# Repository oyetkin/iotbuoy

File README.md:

# IoT Buoy

Lake Erie Algae Bloom 2019, (Image credit NOAA)

An open source, low-cost envirnmental buoy designed to monitor the health of lakes, rivers, estuaries and tidal regions with particular emphasis on algae blooms.
Designed by [Analytical Mechanics Associates](https://www.ama-inc.com/) and the [Virginia Modeling, Analysis & Simulation Center (VMASC)](https://www.odu.edu/vmasc). This project is compatible with the [Open Data Cube](https://www.opendatacube.org/), which is an open-source platform that can ingest data from a variety of sensors and has the goal of making environmental monitoring simple and highly accessible. An overview of the current progress is posted [here](https://github.com/oyetkin/iotbuoy/blob/main/BuoyPresentation1.pdf)

# Building your Buoy - Buoy Specific Hardware Required

### 1. [Arduino MEGA or ELEGOO MEGA](https://www.amazon.com/ELEGOO-ATmega2560-ATMEGA16U2-Arduino-Compliant/dp/B01H4ZDYCE/ref=asc_df_B01H4ZDYCE/?tag=hyprod-20&linkCode=df0&hvadid=309751315916&hvpos=&hvnetw=g&hvrand=11900577637582741809&hvpone=&hvptwo=&hvqmt=&hvdev=c&hvdvcmdl=&hvlocint=&hvlocphy=9008124&hvtargid=pla-493625544636&psc=1&tag=&ref=&adgrpid=67183599252&hvpone=&hvptwo=&hvadid=309751315916&hvpos=&hvnetw=g&hvrand=11900577637582741809&hvqmt=&hvdev=c&hvdvcmdl=&hvlocint=&hvlocphy=9008124&hvtargid=pla-493625544636)

- [Arduino MEGA R3](https://store.arduino.cc/usa/mega-2560-r3)

- [ELEGOO MEGA R3 (cheaper)](https://www.amazon.com/ELEGOO-ATmega2560-ATMEGA16U2-Arduino-Compliant/dp/B01H4ZDYCE/ref=asc_df_B01H4ZDYCE/?tag=hyprod-20&linkCode=df0&hvadid=309751315916&hvpos=&hvnetw=g&hvrand=11900577637582741809&hvpone=&hvptwo=&hvqmt=&hvdev=c&hvdvcmdl=&hvlocint=&hvlocphy=9008124&hvtargid=pla-493625544636&psc=1&tag=&ref=&adgrpid=67183599252&hvpone=&hvptwo=&hvadid=309751315916&hvpos=&hvnetw=g&hvrand=11900577637582741809&hvqmt=&hvdev=c&hvdvcmdl=&hvlocint=&hvlocphy=9008124&hvtargid=pla-493625544636)

### 2. [Adafruit Boost Converter](https://www.amazon.com/Module-Output-Voltage-Converter-Regulator/dp/B08NCM9ZPQ/ref=pd_lpo_2?pd_rd_i=B08NCM9ZPQ&th=1)

### 3. [SIM 808 GPRS/GSM Shield](https://www.robotshop.com/en/sim808-gps-gprsgsm-arduino-shield-mkf.html)

### 4. [Adafruit Solar Charger](https://www.adafruit.com/product/390?gclid=Cj0KCQiAkZKNBhDiARIsAPsk0Wjwwub03ZPgBxlKg1lHWn5nn0opyzVy_Q3VPSugYz3q11KsZ251EOcaAhBzEALw_wcB)

### 5. [Adafruit Data Logging Shield](https://www.adafruit.com/product/1141?gclid=EAIaIQobChMI9OqQ1tr58QIVzXxvBB3GTgbGEAQYASABEgITQvD_BwE)

- Requires [CR1220 Coin Cell Battery](https://www.grainger.com/product/54ZU79?ef_id=CjwKCAjwmeiIBhA6EiwA-uaeFeCfQyJyafe8bUuabPpTv9V-Dkiohqq99VO3asoSj661ExP630XgBhoCccUQAvD_BwE:G:s&s_kwcid=AL!2966!3!496359975085!!!g!484329633033!&gucid=N:N:PS:Paid:GGL:CSM-2293:99F1R6:20501231&gclid=CjwKCAjwmeiIBhA6EiwA-uaeFeCfQyJyafe8bUuabPpTv9V-Dkiohqq99VO3asoSj661ExP630XgBhoCccUQAvD_BwE&gclsrc=aw.ds)

- [Adafruit Data Logging Shield Board and Schematic](https://github.com/adafruit/Data-Logger-shield)

- [Adafruit Data Logging Shield Fritzing Object](https://github.com/adafruit/Fritzing-Library/blob/master/parts/Adafruit%20Datalogger%20Shield%20v1.fzpz)

### 6. [Adafruit ADS1115 Analog to Digital Converter](https://www.adafruit.com/product/1085?gclid=Cj0KCQjw0emHBhC1ARIsAL1QGNfJ3SJ85uZqejbk4At3gi_rBteSZwTxbq5_mKbJvcHG9wJhS_kqJ54aAu4vEALw_wcB)

- [ADS1115 Hardware Drivers](https://github.com/adafruit/Adafruit_ADS1X15)

- [ADS1115 Board and Schematics](https://github.com/adafruit/ADS1X15-Breakout-Board-PCBs)

- [ADS1115 Fritzing Object](https://github.com/adafruit/Fritzing-Library/blob/master/parts/Adafruit%20ADS1115%2016Bit%20I2C%20ADC.fzpz)

- [ADS1115 Data Sheet](https://cdn-shop.adafruit.com/datasheets/ads1115.pdf)

- [ADS1115 Sample Code](https://learn.adafruit.com/adafruit-4-channel-adc-breakouts/arduino-code)

### 7. [Adafruit 6V 3.5W Solar Panel](https://www.adafruit.com/product/500)

- [Solar Panel Technical Drawing](https://github.com/VoltaicEngineering/Solar-Panel-Drawings/blob/master/Voltaic%20Systems%203.5W%206V%20113x210mm%20DRAWING%20CURRENT%202017%207%2020.pdf)

### 10. [6600 mAh 3.7V Lithium Ion Battery](https://www.adafruit.com/product/353)

### 11. [Adafruit TPL5110 Breakout Board](https://www.adafruit.com/product/3435)

### 12. [Adafruit Power Boost 1000 Breakout Board](https://www.adafruit.com/product/2465?gclid=CjwKCAiA24SPBhB0EiwAjBgkhrGJI_mgLnF6EL7C2EgxJwRfddbmznOh6DxHYULQIVquQbLt4znxhRoCKecQAvD_BwE)

### 12. Housing
- Buoy with CAD files provided [here](https://github.com/oyetkin/iotbuoy/tree/main/CAD_Files)

- Waterproof box

- Your own design

# Fluorometer Design

### 1. [1 x 395 nm LED](https://www.mouser.com/ProductDetail/BIVAR/UV5TZ-390-15?qs=sGAEpiMZZMtaWn5d0uiAD8cVjFdgDZGx%2FUxBqCDWrPM%3D)

### 2. [FDS 100 Photodiode](https://www.thorlabs.us/thorproduct.cfm?partnumber=FDS100)

### 3. [550 nm Cut On Long Pass Filter](https://www.newport.com/p/10CGA-550)

### 4. [Jewler's Resin](https://www.amazon.com/16OZ-Epoxy-Resin-Graduated-Instructions/dp/B0839GN3PF/ref=sr_1_5?keywords=clear%2Bepoxy%2Bresin&qid=1638217693&qsid=146-2373950-0512811&s=arts-crafts&sr=1-5&sres=B08233BV5W%2CB08HN2XCDS%2CB0839GN3PF%2CB098918WFB%2CB084PZG6HK%2CB07S1MLQMJ%2CB084Q87Y8M%2CB07YCVVYFK%2CB099XFL1PK%2CB086L1CDMT%2CB07G5HY79C%2CB07JBKDQZJ%2CB07JB5P76Z%2CB089XZJFG5%2CB097JLGFZF%2CB07QF2XYYX%2CB092HX7SQT%2CB08PF576QC%2CB0823LC5H1%2CB08XQ2S1VQ&th=1)

### 5. [Black ABS Filament (will be useful for turbidity sensor as well)](https://www.amazon.com/HATCHBOX-3D-Filament-Dimensional-Accuracy/dp/B00J0H8EWA/ref=sr_1_3?crid=HBAP4Q1YHOWB&keywords=black%2Babs%2Bfilament%2B1.75%2B1kg&qid=1638217775&qsid=146-2373950-0512811&sprefix=black%2Babs%2Bfila%2Carts-crafts%2C167&sr=8-3&sres=B00J0H8EWA%2CB07XF5KM74%2CB07T2QZSLY%2CB01M6Y2QF1%2CB00MV7T25E%2CB07199449V%2CB00WX4UONO%2CB0919Q91MN%2CB015VGJGPW%2CB00F9MNMAY%2CB018F586ES%2CB08N4MMK6V%2CB089NPTH2W%2CB09H7RKL95%2CB07GFXYVLR%2CB08BR7YCY1&srpt=THERMOPLASTIC_FILAMENT&th=1)

# Turbidity Sensor Design

### 1. [2 x Photoresistors](https://www.amazon.com/gp/product/B01N7V536K/ref=ppx_yo_dt_b_search_asin_image?ie=UTF8&psc=1)

### 2. [1 x RGB LED](https://www.amazon.com/gp/product/B077XGF3YR/ref=ppx_yo_dt_b_search_asin_title?ie=UTF8&th=1)

### 3. [Jewler's Resin](https://www.amazon.com/16OZ-Epoxy-Resin-Graduated-Instructions/dp/B0839GN3PF/ref=sr_1_5?keywords=clear%2Bepoxy%2Bresin&qid=1638217693&qsid=146-2373950-0512811&s=arts-crafts&sr=1-5&sres=B08233BV5W%2CB08HN2XCDS%2CB0839GN3PF%2CB098918WFB%2CB084PZG6HK%2CB07S1MLQMJ%2CB084Q87Y8M%2CB07YCVVYFK%2CB099XFL1PK%2CB086L1CDMT%2CB07G5HY79C%2CB07JBKDQZJ%2CB07JB5P76Z%2CB089XZJFG5%2CB097JLGFZF%2CB07QF2XYYX%2CB092HX7SQT%2CB08PF576QC%2CB0823LC5H1%2CB08XQ2S1VQ&th=1)

### 4. [Black ABS Filament (will be useful for fluorometer as well)](https://www.amazon.com/HATCHBOX-3D-Filament-Dimensional-Accuracy/dp/B00J0H8EWA/ref=sr_1_3?crid=HBAP4Q1YHOWB&keywords=black%2Babs%2Bfilament%2B1.75%2B1kg&qid=1638217775&qsid=146-2373950-0512811&sprefix=black%2Babs%2Bfila%2Carts-crafts%2C167&sr=8-3&sres=B00J0H8EWA%2CB07XF5KM74%2CB07T2QZSLY%2CB01M6Y2QF1%2CB00MV7T25E%2CB07199449V%2CB00WX4UONO%2CB0919Q91MN%2CB015VGJGPW%2CB00F9MNMAY%2CB018F586ES%2CB08N4MMK6V%2CB089NPTH2W%2CB09H7RKL95%2CB07GFXYVLR%2CB08BR7YCY1&srpt=THERMOPLASTIC_FILAMENT&th=1)

# Other Items Required

- SD Card
- Jumper wires
- Header pins
- Solder
- Soldering iron
- Wire strippers
- Heat shrink tubing
- Electrical tape
- DP 100 epoxy
- Rope/anchor OR Rope/mooring OR free-floating

# Other Interesting Sensors

- [BME 680 Temperature, Pressure and Humidity Sensor](https://www.adafruit.com/product/3660)

- [DHT-11 Temperature/Humidity Sensor](https://www.adafruit.com/product/386)

- [DHT-22 Temperature/Humidity Sensor](https://www.adafruit.com/product/385)

- [Waterproof Thermistor](https://www.adafruit.com/product/372)

- [pH Sensor - TEKCOPLUS](https://www.amazon.com/Replacement-Electrode-Connector-Controller-Hydroponics/dp/B09681C36B/ref=sr_1_19?dchild=1&keywords=ph+meter+electrode&qid=1629149917&sr=8-19)
OR
- [pH Sensor - Vernier](https://www.vernier.com/product/ph-sensor/)

- [Turbidity Sensor](https://www.digikey.com/en/products/detail/amphenol-advanced-sensors/TSD-10/4767843?utm_adgroup=Sensors%20%26%20Transducers&utm_source=google&utm_medium=cpc&utm_campaign=Dynamic%20Search_EN_RLSA_Buyers&utm_term=&utm_content=Sensors%20%26%20Transducers&gclid=CjwKCAjwmeiIBhA6EiwA-uaeFRJvJ3rLHPiHJND-PSO5aePXsmi2i962wfCCjfp96LtXLJMJ6MAUsBoClz0QAvD_BwE)

- [MPU 6050 Inertial Measurement Unit (for wave height, direction etc.)](https://www.adafruit.com/product/3886)

# Fabrication

- Read the "Complete Guide to Building Your Very Own Algae Monitoring Buoy"

# Viewing Results

- Download jupyter to your computer and run "Visualization_Notebook.ipynb"

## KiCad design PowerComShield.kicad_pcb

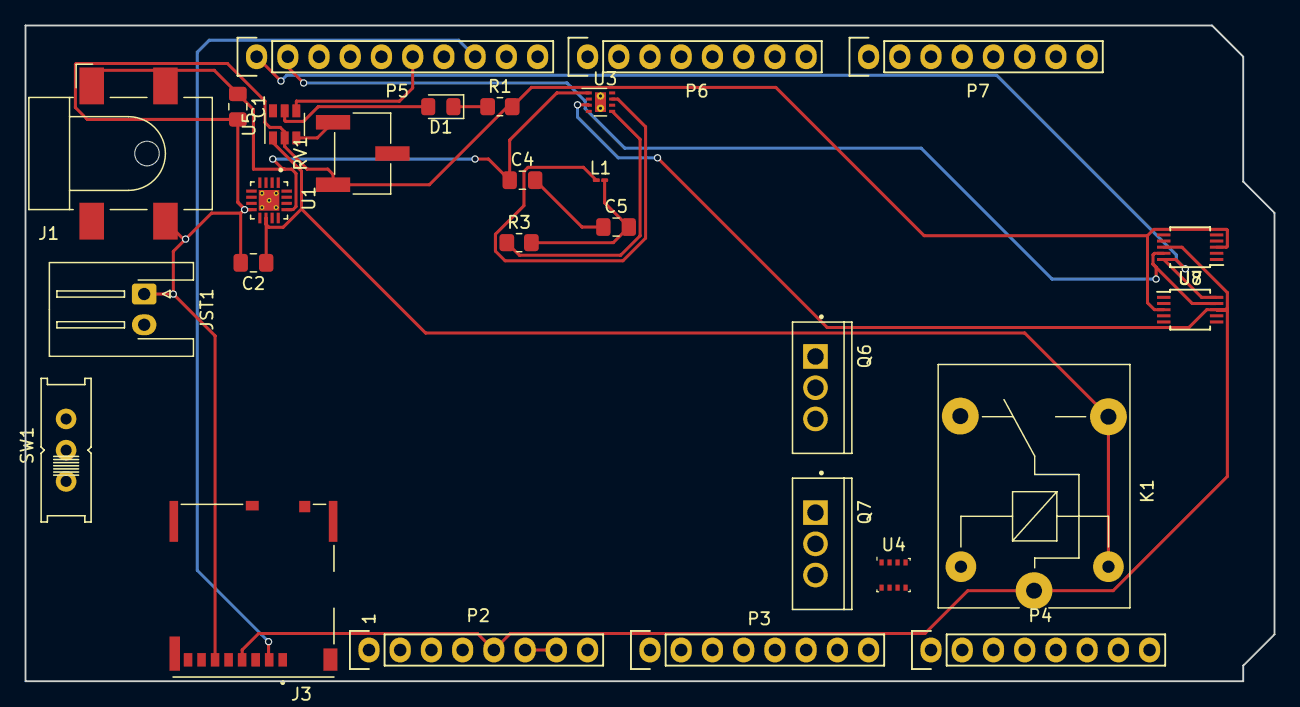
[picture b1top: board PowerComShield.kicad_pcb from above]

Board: 4 copper layers, 101.6 x 53.3 mm, 28 parts (0 on the bottom side), 16 nets.

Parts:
C1: 1uF; C_0805_2012Metric_Pad1.18x1.45mm_HandSolder
C2: 4.7 uF; C_0805_2012Metric_Pad1.18x1.45mm_HandSolder
C4, C5: 10 uF; C_0805_2012Metric_Pad1.18x1.45mm_HandSolder
D1: D; D_0805_2012Metric_Pad1.15x1.40mm_HandSolder
J1: Barrel_Jack; BarrelJack_CLIFF_FC681465S_SMT_Horizontal
J3: Micro_SD_Card; MOLEX_503398-1892
JST1: Conn_01x02; JST_XH_S2B-XH-A-1_1x02_P2.50mm_Horizontal
K1: SANYOU_SRD_Form_C; Relay_SPDT_SANYOU_SRD_Series_Form_C
L1: 15 uH; L_01005_0402Metric_Pad0.57x0.30mm_HandSolder
P2: Power; Socket_Strip_Arduino_1x08
P3, P4: Analog; Socket_Strip_Arduino_1x08
P5: PWM; Socket_Strip_Arduino_1x10
P6: PWM; Socket_Strip_Arduino_1x08
P7: Communication; Socket_Strip_Arduino_1x08
Q6, Q7: Q_PMOS_GDS; TO254P1067X483X3124-3P
R1: 1 MOhm; R_0805_2012Metric_Pad1.20x1.40mm_HandSolder
R3: 400 kohm; R_0805_2012Metric_Pad1.20x1.40mm_HandSolder
RV1: R_POT; Potentiometer_Bourns_3269W_Vertical
SW1: SW_DPDT_x2; EG1218
U1: BQ24075; QFN50P300X300X100-17N
U3: TPS62125DSG; WSON-8-1EP_2x2mm_P0.5mm_EP0.9x1.6mm_ThermalVias
U4: BME280; Bosch_LGA-8_2.5x2.5mm_P0.65mm_ClockwisePinNumbering
U5: TPL5110; SOT-23-6
U7, U8: ADS1115IDGS; TSSOP-10_3x3mm_P0.5mm

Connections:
+5V: J3.4, K1.1, P2.5, U3.2, U3.3, U7.8, U8.8
/10(**): J3.2, P5.8
/12(**): P5.6, U5.4
/SCL: P5.1, U7.10, U8.10
/SDA: P5.2, U7.9, U8.9
GND: P2.6, P2.7, P5.4
unnamed: C1.1, C4.1, J1.1, U1.13, U3.1
unnamed: C1.2, C2.2, J1.2, J3.6, JST1.1, R1.2, RV1.3, U1.8, U5.2, U7.3, U8.3
unnamed: C2.1, K1.2, K1.3, U1.10, U5.1
unnamed: C4.2, C5.1
unnamed: C5.2, L1.2, R3.2
unnamed: D1.1, R1.1
unnamed: D1.2, U5.5
unnamed: L1.1, U3.7
unnamed: R3.1, U3.5
unnamed: RV1.1, U5.3

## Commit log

2021-08-24 Add files via upload
    This file allows the user to upload data from a device connected to a personal computer directly to the IoT server. This is useful particularly for streaming data using LoRa or other radio communicat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
2021-08-31 Add files via upload
    Working example for GPRS/RTC. You must bend pins 7/8 and 0/1 (TX/RX) on the arduino GPRS shield if you are using an arduino mega.
2021-10-04 Add files via upload
    Updated thermistor code
2021-10-04 Add files via upload
    Added pH calibration
2021-10-07 Create Fluorometer
2021-12-27 Add files via upload
    The initial prototype for power and data management shield for the buoy.
2022-03-16 Add files via upload
    Buoy deployment with just a fluorometer for simplicity
